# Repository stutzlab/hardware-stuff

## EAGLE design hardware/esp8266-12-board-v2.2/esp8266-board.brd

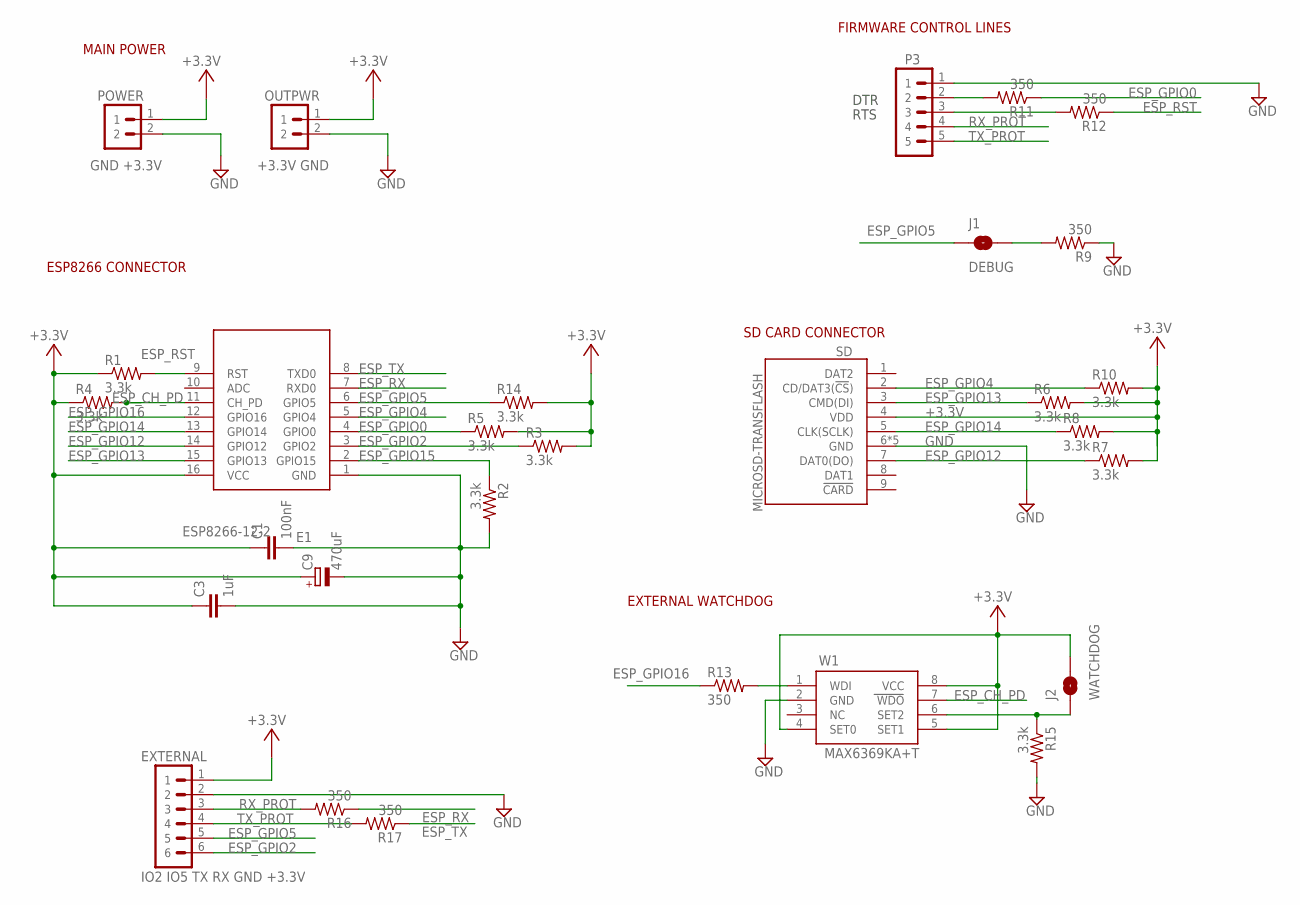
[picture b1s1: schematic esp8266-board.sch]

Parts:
C1: 100nF; SMD0805
C3: 1uF; SMD0805
C9: 470uF; E2,5-6
E1: ESP8266-12-2
EXTERNAL: IO2 IO5 TX RX GND +3.3V; PIN-HEADER-6PIN
J1: DEBUG; JUMPER-PAD-2-ROUND
J2: WATCHDOG; JUMPER-PAD-2-ROUND
OUTPWR: +3.3V GND; PIN-HEADER-2PIN
P3: GND DTR RTS RX TX; PIN-HEADER-5PIN
POWER: GND +3.3V; PIN-HEADER-2PIN
R1, R2, R3, R4, R5, R6, R7, R8, R10, R14, R15: 3.3k; SMD0805
R9, R11, R12, R13, R16, R17: 350; SMD0805
SD: MICROSD-TRANSFLASH
W1: MAX6369KA+T; SOT23-8

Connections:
+3.3V: C1.1, C3.1, C9.+, E1.16 (VCC), EXTERNAL.1, J2.2, OUTPWR.1, POWER.1, R1.1, R3.2, R4.1, R5.2, R6.2, R7.2, R8.2, R10.2, R14.2, SD.4 (VDD), W1.4 (SET0), W1.5 (SET1), W1.8 (VCC)
ESP_CH_PD: E1.11 (CH_PD), R4.2, W1.7 (WDO)
ESP_GPIO0: E1.4 (GPIO0), R5.1, R11.1
ESP_GPIO2: E1.3 (GPIO2), EXTERNAL.6, R3.1
ESP_GPIO4: E1.5 (GPIO4), R10.1, SD.2 (CD/DAT3(!CS!))
ESP_GPIO5: E1.6 (GPIO5), EXTERNAL.5, J1.1, R14.1
ESP_GPIO12: E1.14 (GPIO12), R7.1, SD.7 (DAT0(DO))
ESP_GPIO13: E1.15 (GPIO13), R6.1, SD.3 (CMD(DI))
ESP_GPIO14: E1.13 (GPIO14), R8.1, SD.5 (CLK(SCLK))
ESP_GPIO15: E1.2 (GPIO15), R2.1
ESP_GPIO16: E1.12 (GPIO16), R13.1
ESP_RST: E1.9 (RST), R1.2, R12.1
ESP_RX: E1.7 (RXD0), R16.1
ESP_TX: E1.8 (TXD0), R17.1
GND: C1.2, C3.2, C9.-, E1.1 (GND), EXTERNAL.2, OUTPWR.2, P3.1, POWER.2, R2.2, R9.1, R15.2, SD.6 (GND), SD.S1 (GND), SD.S2 (GND), SD.S3 (GND), SD.S4 (GND), W1.2 (GND)
unnamed: J2.1, R15.1, W1.6 (SET2)
unnamed: J1.2, R9.2
unnamed: P3.2, R11.2
unnamed: P3.3, R12.2
unnamed: R13.2, W1.1 (WDI)
RX_PROT: EXTERNAL.3, P3.4, R16.2
TX_PROT: EXTERNAL.4, P3.5, R17.2

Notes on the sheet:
MAIN POWER
ESP8266 CONNECTOR
FIRMWARE CONTROL LINES
DTR
RTS
SD CARD CONNECTOR
EXTERNAL WATCHDOG

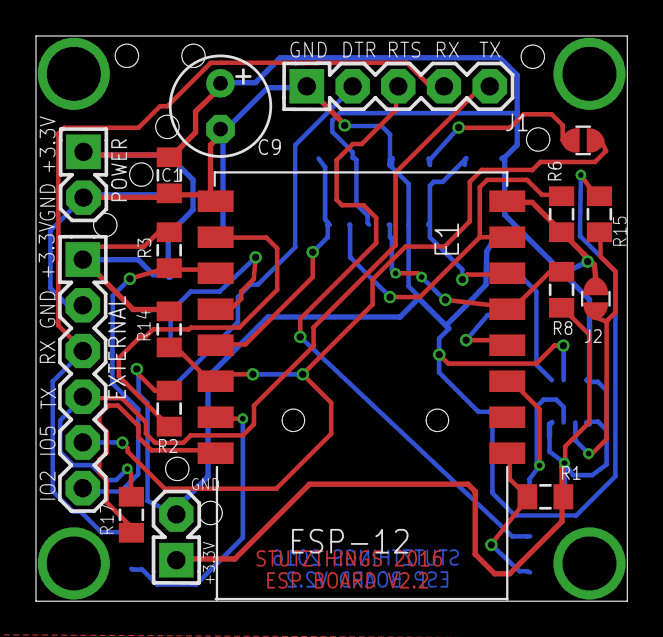
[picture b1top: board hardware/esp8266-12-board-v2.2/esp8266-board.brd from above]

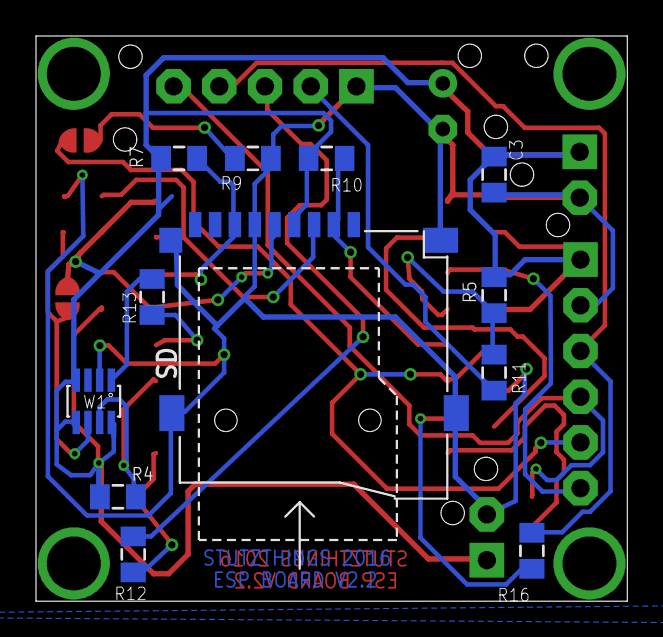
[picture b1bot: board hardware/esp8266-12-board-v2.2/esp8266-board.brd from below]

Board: 2 copper layers, 32.9 x 31.4 mm, 29 parts (12 on the bottom side), 22 nets.

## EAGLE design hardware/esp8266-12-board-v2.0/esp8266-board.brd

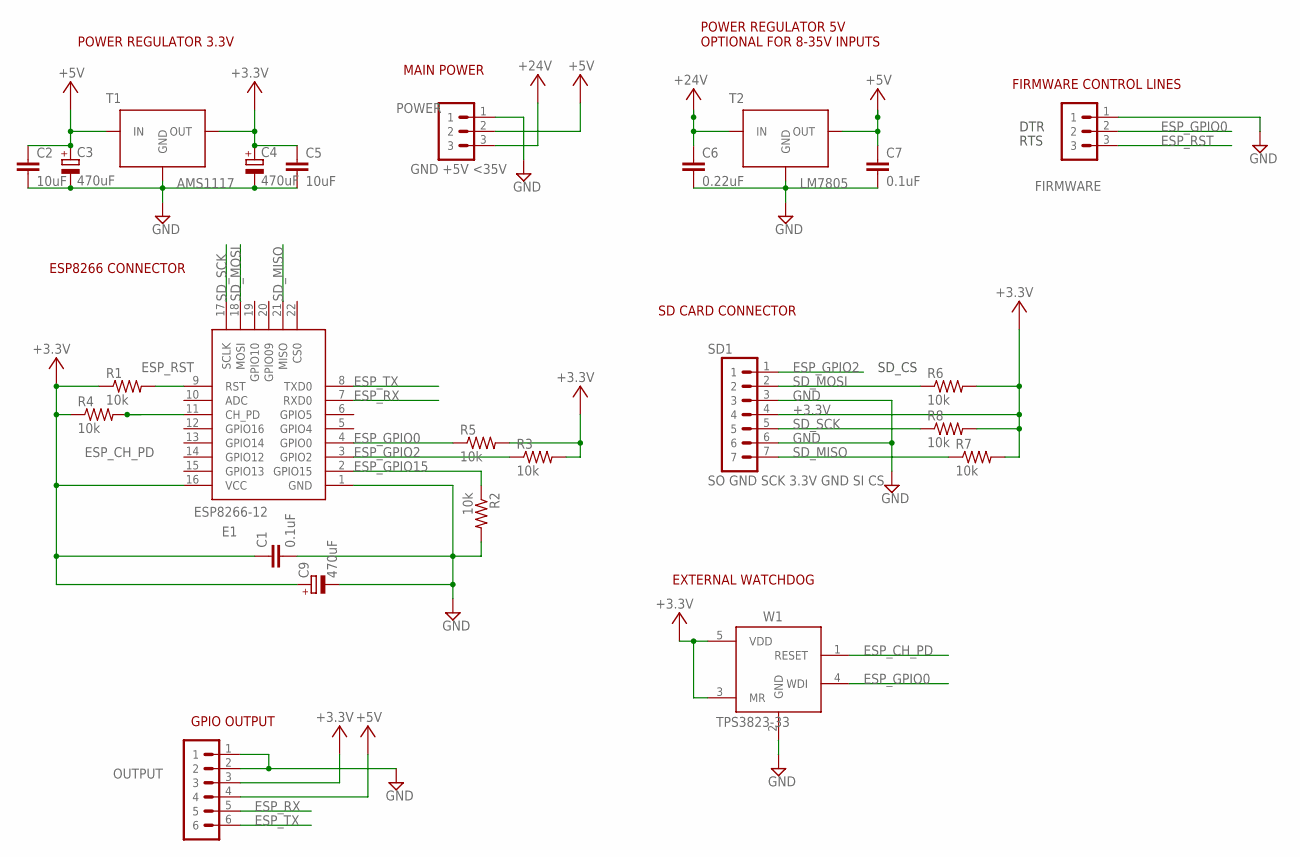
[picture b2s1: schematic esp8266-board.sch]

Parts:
C1: 0.1uF; C2.5-2
C2, C5: 10uF; C2.5-2
C3: 470uF; E2,5-6E
C4: 470uF; E2,5-6E; MPN FK18X5R0J106M
C6: 0.22uF; C2.5-2; MPN 1C10Z5U104M050B
C7: 0.1uF; C2.5-2; MPN FK18X5R0J106M
C9: 470uF; E2,5-6
E1: ESP8266-12
FIRMWARE: GND DTR RTS; PIN-HEADER-3PIN
OUTPUT: GND GND 3.3V 5V RX TX; PIN-HEADER-6PIN
POWER: GND +5V <35V; PIN-HEADER-3PIN
R1, R2, R3, R4, R5, R6, R7, R8: 10k; RESISTOR-V1
SD1: SO GND SCK 3.3V GND SI CS; PIN-HEADER-7PIN
T1: AMS1117; SOT-223; MPN LM2937ET-3.3
T2: LM7805; TO-220; MPN LM2937ET-3.3
W1: TPS3823-33; SOT23-5/TSOT25

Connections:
+3.3V: C1.1, C4.+, C5.1, C9.+, E1.16 (VCC), OUTPUT.3, R1.1, R3.2, R4.1, R5.2, R6.2, R7.2, R8.2, SD1.4, T1.2 (OUT), W1.3 (MR), W1.5 (VDD)
+5V: C2.1, C3.+, C7.1, OUTPUT.4, POWER.2, T1.3 (IN), T2.OUTPUT (OUT)
+24V: C6.1, POWER.3, T2.INPUT (IN)
ESP_CH_PD: E1.11 (CH_PD), R4.2, W1.1 (RESET)
ESP_GPIO0: E1.4 (GPIO0), FIRMWARE.2, R5.1, W1.4 (WDI)
ESP_GPIO2: E1.3 (GPIO2), R3.1, SD1.1
ESP_GPIO15: E1.2 (GPIO15), R2.1
ESP_RST: E1.9 (RST), FIRMWARE.3, R1.2
ESP_RX: E1.7 (RXD0), OUTPUT.5
ESP_TX: E1.8 (TXD0), OUTPUT.6
GND: C1.2, C2.2, C3.-, C4.-, C5.2, C6.2, C7.2, C9.-, E1.1 (GND), FIRMWARE.1, OUTPUT.1, OUTPUT.2, POWER.1, R2.2, SD1.3, SD1.6, T1.1 (GND), T2.GND, W1.2 (GND)
GPIO5: E1.6 (GPIO5)
SD_MISO: E1.21 (MISO), R7.1, SD1.7
SD_MOSI: E1.18 (MOSI), R6.1, SD1.2
SD_SCK: E1.17 (SCLK), R8.1, SD1.5

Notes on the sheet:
POWER REGULATOR 3.3V
MAIN POWER
ESP8266 CONNECTOR
FIRMWARE CONTROL LINES
GPIO OUTPUT
POWER REGULATOR 5V OPTIONAL FOR 8-35V INPUTS
DTR
RTS
SD CARD CONNECTOR
SD_CS
EXTERNAL WATCHDOG

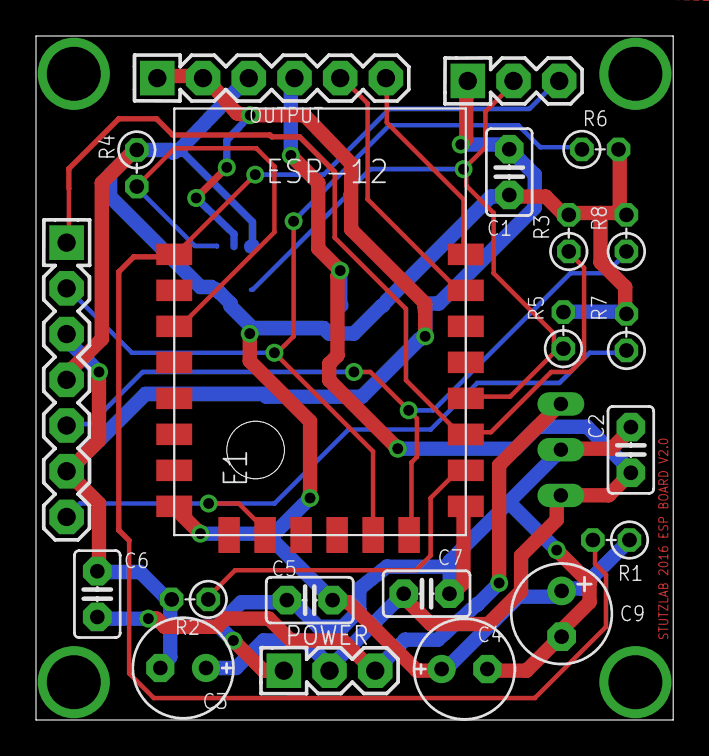
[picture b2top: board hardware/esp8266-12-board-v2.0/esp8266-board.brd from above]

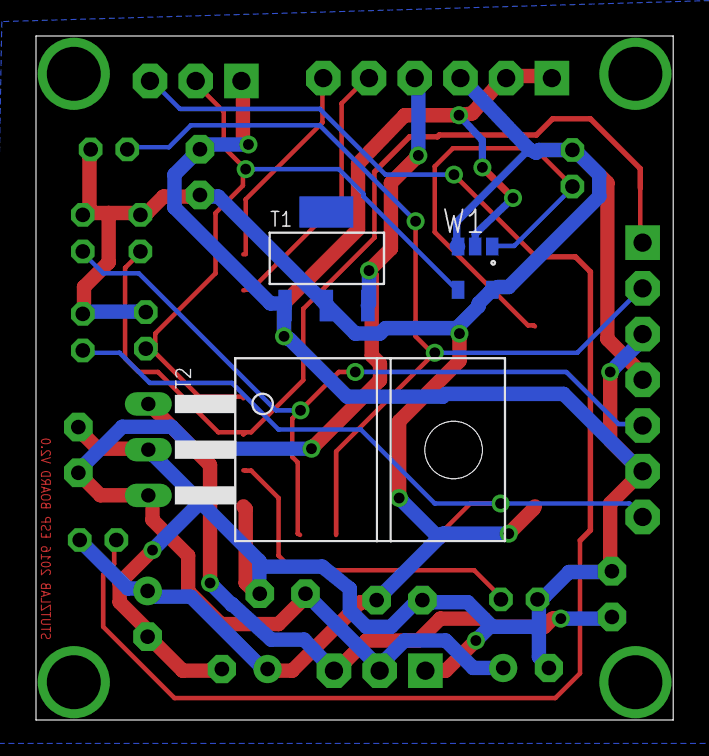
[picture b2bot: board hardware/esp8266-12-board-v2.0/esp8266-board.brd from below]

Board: 2 copper layers, 35.4 x 38.0 mm, 24 parts (3 on the bottom side), 14 nets.

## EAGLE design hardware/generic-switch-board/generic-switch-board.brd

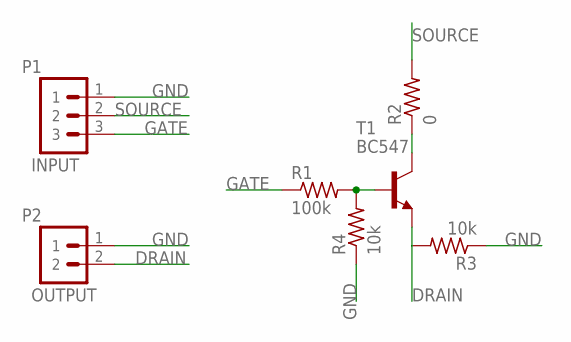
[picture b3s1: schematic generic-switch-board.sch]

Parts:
P1: IN; PIN-HEADER-3PIN
P2: OUT; PIN-HEADER-2PIN
R1: 100k; RESISTOR-V3
R2: 0; RESISTOR-V2
R3, R4: 10k; RESISTOR-V1
T1: BC547; TO-92-FLAT

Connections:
DRAIN: P2.2, R3.2, T1.1 (E)
GATE: P1.3, R1.1
GND: P1.1, P2.1, R3.1, R4.1
unnamed: R1.2, R4.2, T1.2 (B)
unnamed: R2.1, T1.3 (C)
SOURCE: P1.2, R2.2

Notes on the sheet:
INPUT
OUTPUT

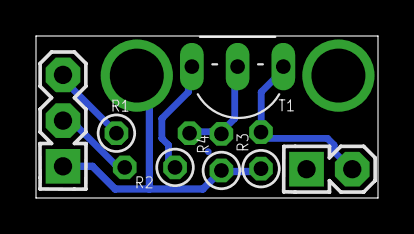
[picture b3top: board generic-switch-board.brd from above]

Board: 2 copper layers, 19.0 x 9.0 mm, 7 parts (0 on the bottom side), 6 nets.

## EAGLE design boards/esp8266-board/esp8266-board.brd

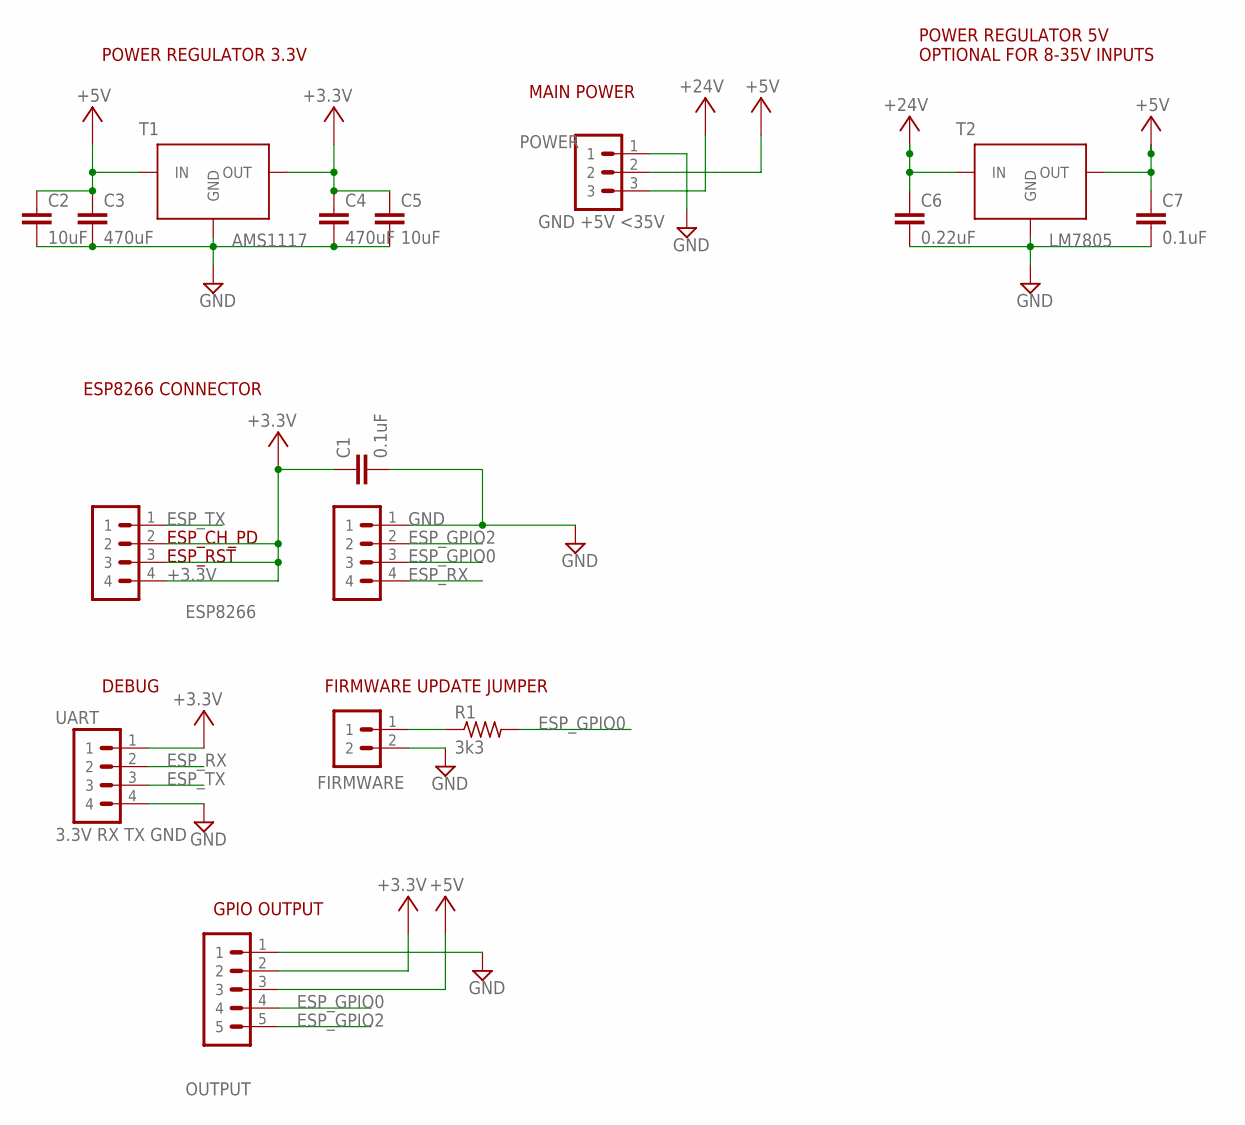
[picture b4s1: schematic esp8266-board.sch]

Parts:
C1: 0.1uF; C2.5-2
C2, C5: 10uF; C2.5-2
C3: 470uF; C2.5-2; MPN 1C10Z5U104M050B
C4: 470uF; C2.5-2; MPN FK18X5R0J106M
C6: 0.22uF; C2.5-2; MPN 1C10Z5U104M050B
C7: 0.1uF; C2.5-2; MPN FK18X5R0J106M
FIRMWARE: FIRMWARE; PIN-HEADER-2PIN
OUTPUT: GND 3.3V 5V IO0 IO2; PIN-HEADER-5PIN
P1: ESP8266; PIN-HEADER-4PIN
P2: ESP8266 CONNECTOR; PIN-HEADER-4PIN
POWER: GND +5V <35V; PIN-HEADER-3PIN
R1: 3k3; RESISTOR-V2
T1: AMS1117; SOT-223; MPN LM2937ET-3.3
T2: LM7805; TO-220; MPN LM2937ET-3.3
UART: 3.3V RX TX GND; PIN-HEADER-4PIN

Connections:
+3.3V: C1.1, C4.1, C5.1, OUTPUT.2, P1.2, P1.3, P1.4, T1.2 (OUT), UART.1
+5V: C2.1, C3.1, C7.1, OUTPUT.3, POWER.2, T1.3 (IN), T2.OUTPUT (OUT)
+24V: C6.1, POWER.3, T2.INPUT (IN)
ESP_GPIO0: OUTPUT.4, P2.3, R1.2
ESP_GPIO2: OUTPUT.5, P2.2
ESP_RX: P2.4, UART.2
ESP_TX: P1.1, UART.3
GND: C1.2, C2.2, C3.2, C4.2, C5.2, C6.2, C7.2, FIRMWARE.2, OUTPUT.1, P2.1, POWER.1, T1.1 (GND), T2.GND, UART.4
unnamed: FIRMWARE.1, R1.1

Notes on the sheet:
POWER REGULATOR 3.3V
ESP_CH_PD
ESP_RST
DEBUG
MAIN POWER
ESP8266 CONNECTOR
FIRMWARE UPDATE JUMPER
GPIO OUTPUT
POWER REGULATOR 5V OPTIONAL FOR 8-35V INPUTS

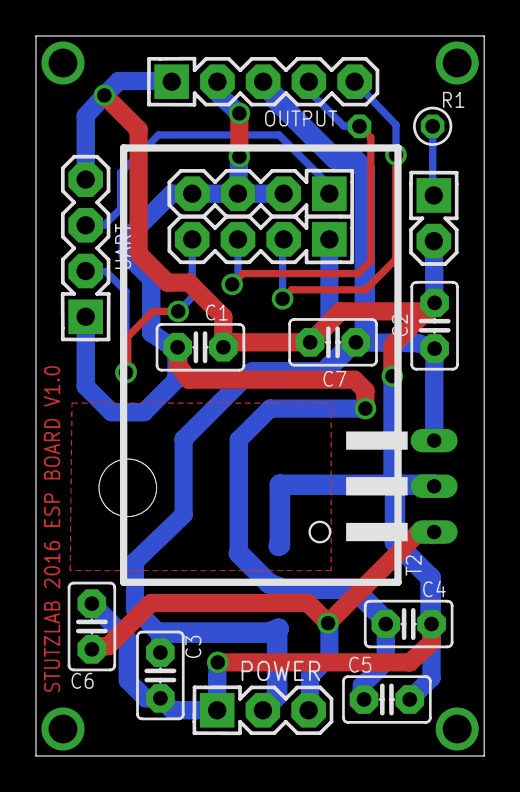
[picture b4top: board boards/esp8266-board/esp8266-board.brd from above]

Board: 2 copper layers, 24.9 x 40.0 mm, 16 parts (1 on the bottom side), 9 nets.

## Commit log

2016-04-04 Added 3, 5 PINS to eagle lib
2016-04-23 Finished routing PCB
2016-04-23 Board review
2016-04-23 Added git ignore
2016-04-23 gitignore
2016-04-23 Removing backup
2016-04-27 ESP8266 board updating
2016-04-27 ESP8266 board update
2016-05-03 generic switch board creation
2016-06-12 Watchdog and SD card addition to ESP12E
2016-08-06 commiting uncommited changes
2016-09-17 upload part name
2016-09-28 updated PCB design during first board assembly
2016-09-28 created git ignore
2016-09-28 updated gitignore
2016-11-12 just after notebook crash
2016-11-25 Added watchdog from maxim
2016-12-01 Updating board for SMD usage
2016-12-03 PCB revision to v2.1
2016-12-04 esp8266 2.1 pcb sent to seeed studio
2016-12-24 updated pcb after first manufacturing impressions
2020-01-18 adding second version modifications
